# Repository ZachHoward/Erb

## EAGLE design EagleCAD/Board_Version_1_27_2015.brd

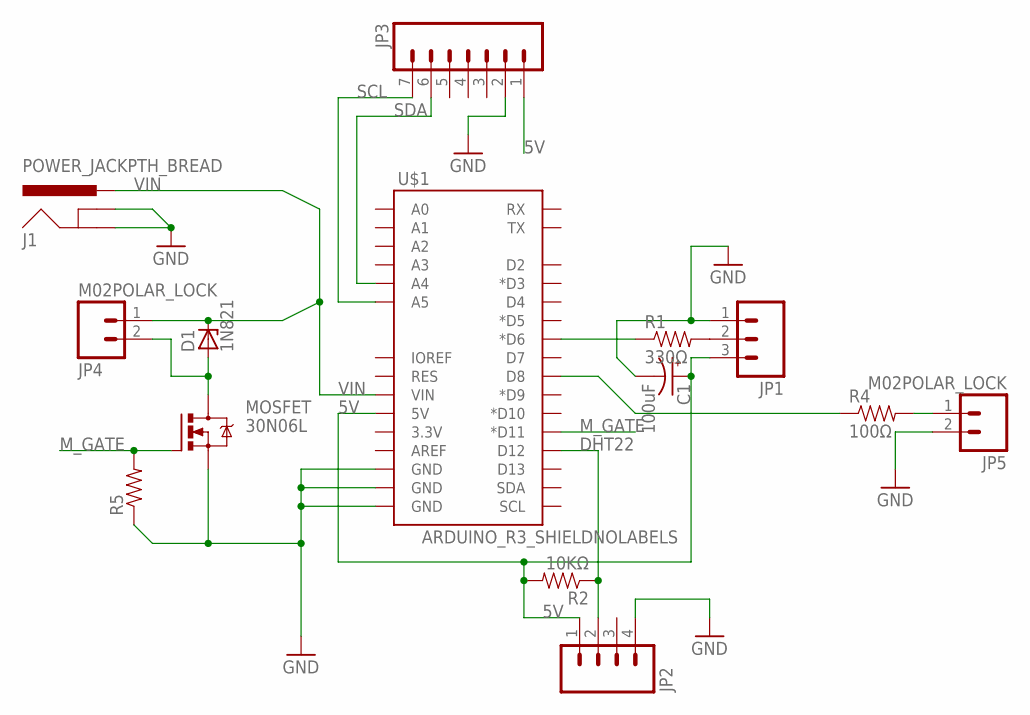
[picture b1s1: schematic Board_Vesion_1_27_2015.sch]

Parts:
C1: 100uF; CPOL-RADIAL-10UF-25V
D1: 1N821; DO35Z10
J1: POWER_JACKPTH_BREAD; POWER_JACK_PTH_BREAD
JP1: M03LOCK_LONGPADS; 1X03_LOCK_LONGPADS
JP2: M04LOCK_LONGPADS; 1X04_LOCK_LONGPADS
JP3: M07LOCK_LONGPADS; 1X07_LOCK_LONGPADS
JP4, JP5: M02POLAR_LOCK; MOLEX-1X2_LOCK
MOSFET: 30N06L; TO220BV
R1: 330Ω; AXIAL-0.4
R2: 10KΩ; AXIAL-0.4
R4: 100Ω; AXIAL-0.4
R5: RESISTORPTH-1W; AXIAL-0.6
U$1: ARDUINO_R3_SHIELDNOLABELS; UNO_R3_SHIELD_NOLABELS

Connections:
5V: C1.1 (+), JP1.3, JP2.1, JP3.1, R2.P$2 (2), U$1.5V
DHT22: JP2.2, R2.P$1 (1), U$1.D12
GND: C1.2 (-), J1.GND, J1.GNDBREAK, JP1.1, JP2.4, JP3.2, JP5.2, MOSFET.S, R5.P$1 (1), U$1.GND@0 (GND), U$1.GND@1 (GND), U$1.GND@2 (GND)
M_GATE: MOSFET.G, R5.P$2 (2), U$1.D11 (*D11)
unnamed: JP1.2, R1.P$2 (2)
unnamed: R4.P$1 (1), U$1.D8
unnamed: R1.P$1 (1), U$1.D6 (*D6)
unnamed: D1.A, JP4.2, MOSFET.D
unnamed: JP5.1, R4.P$2 (2)
SCL: JP3.7, U$1.A5
SDA: JP3.6, U$1.A4
VIN: D1.C, J1.PWR, JP4.1, U$1.VIN

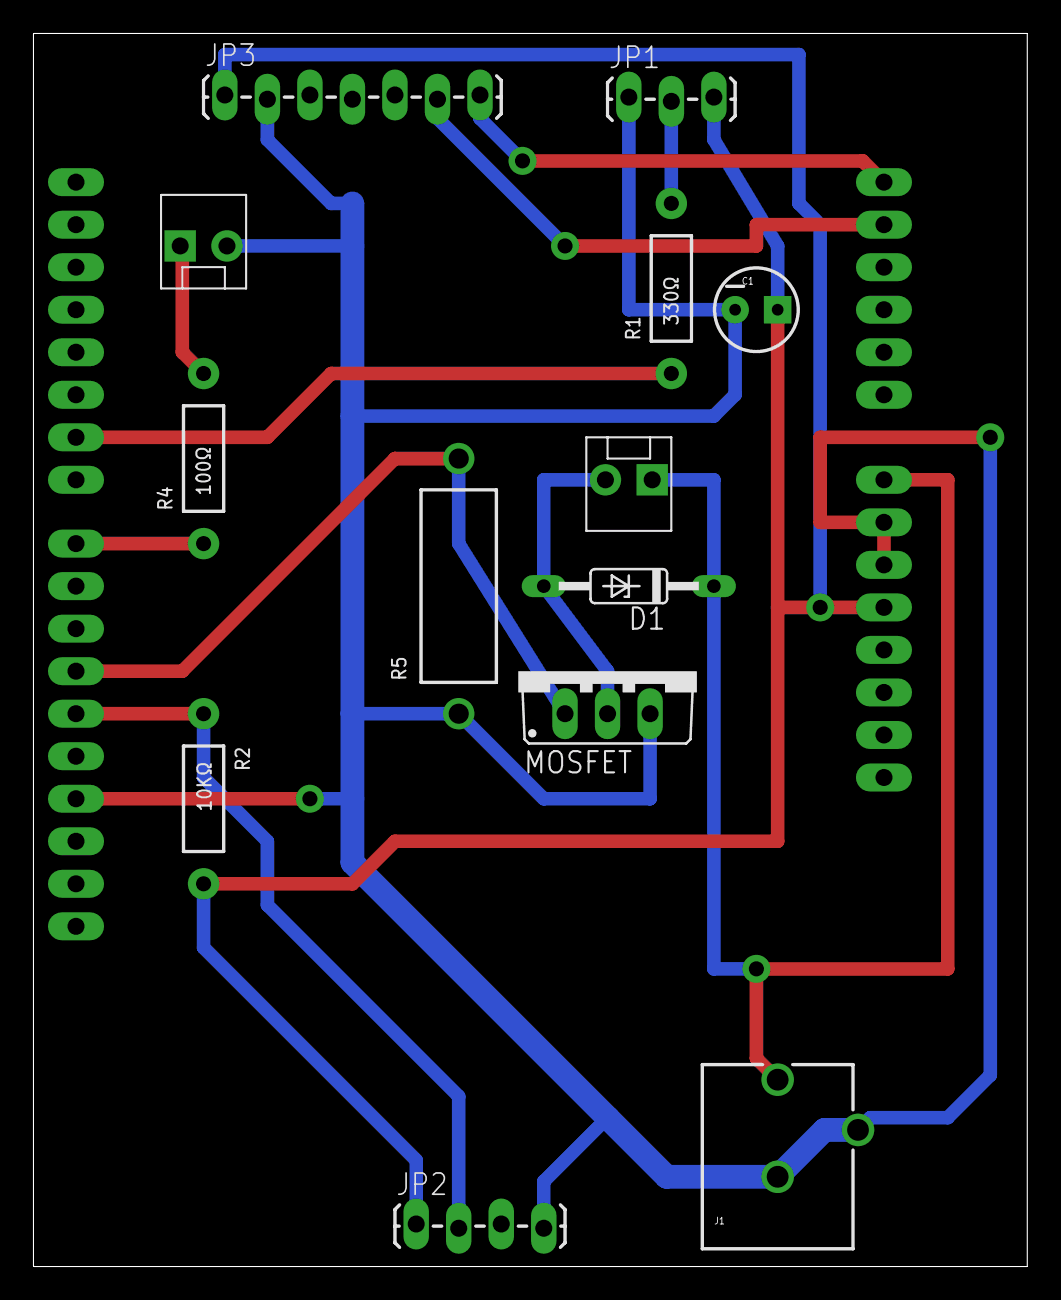
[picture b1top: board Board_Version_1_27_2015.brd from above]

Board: 2 copper layers, 59.4 x 73.7 mm, 14 parts (0 on the bottom side), 12 nets.

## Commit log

2015-01-27 Initial Commit
    Contains Erb code and schematics as currently used in prototype
2015-01-27 Reorganizing file structures
2015-01-27 Branch Work
2015-01-27 Reliability Test Update
    Water, Light and Temperature visual cues and responses are working
    reliably
2015-01-28 All Responses Reliable
    Needs some commenting and code cleaning but it all works
2015-01-28 Fixed Bugs
    All messages were reading errors, added “feeling” message

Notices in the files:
parts and their libraries:
SparkFun-Boards: Licensing: Creative Commons ShareAlike 4.0 International - https://creativecommons.org/licenses/by-sa/4.0
